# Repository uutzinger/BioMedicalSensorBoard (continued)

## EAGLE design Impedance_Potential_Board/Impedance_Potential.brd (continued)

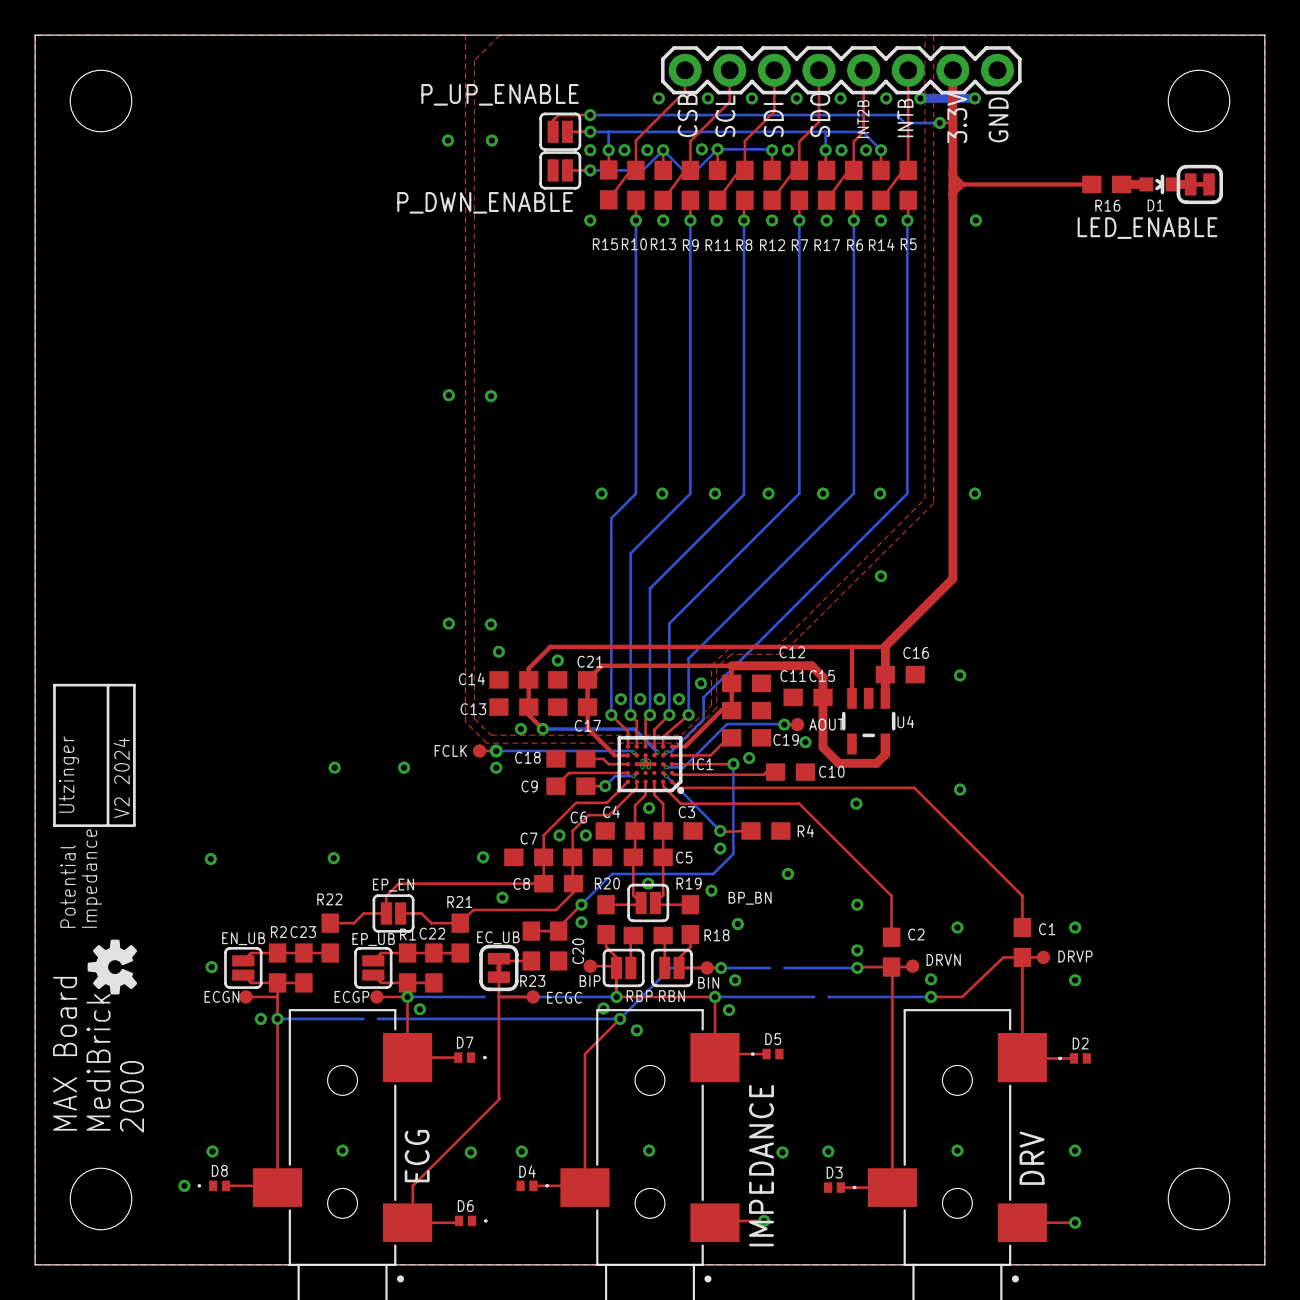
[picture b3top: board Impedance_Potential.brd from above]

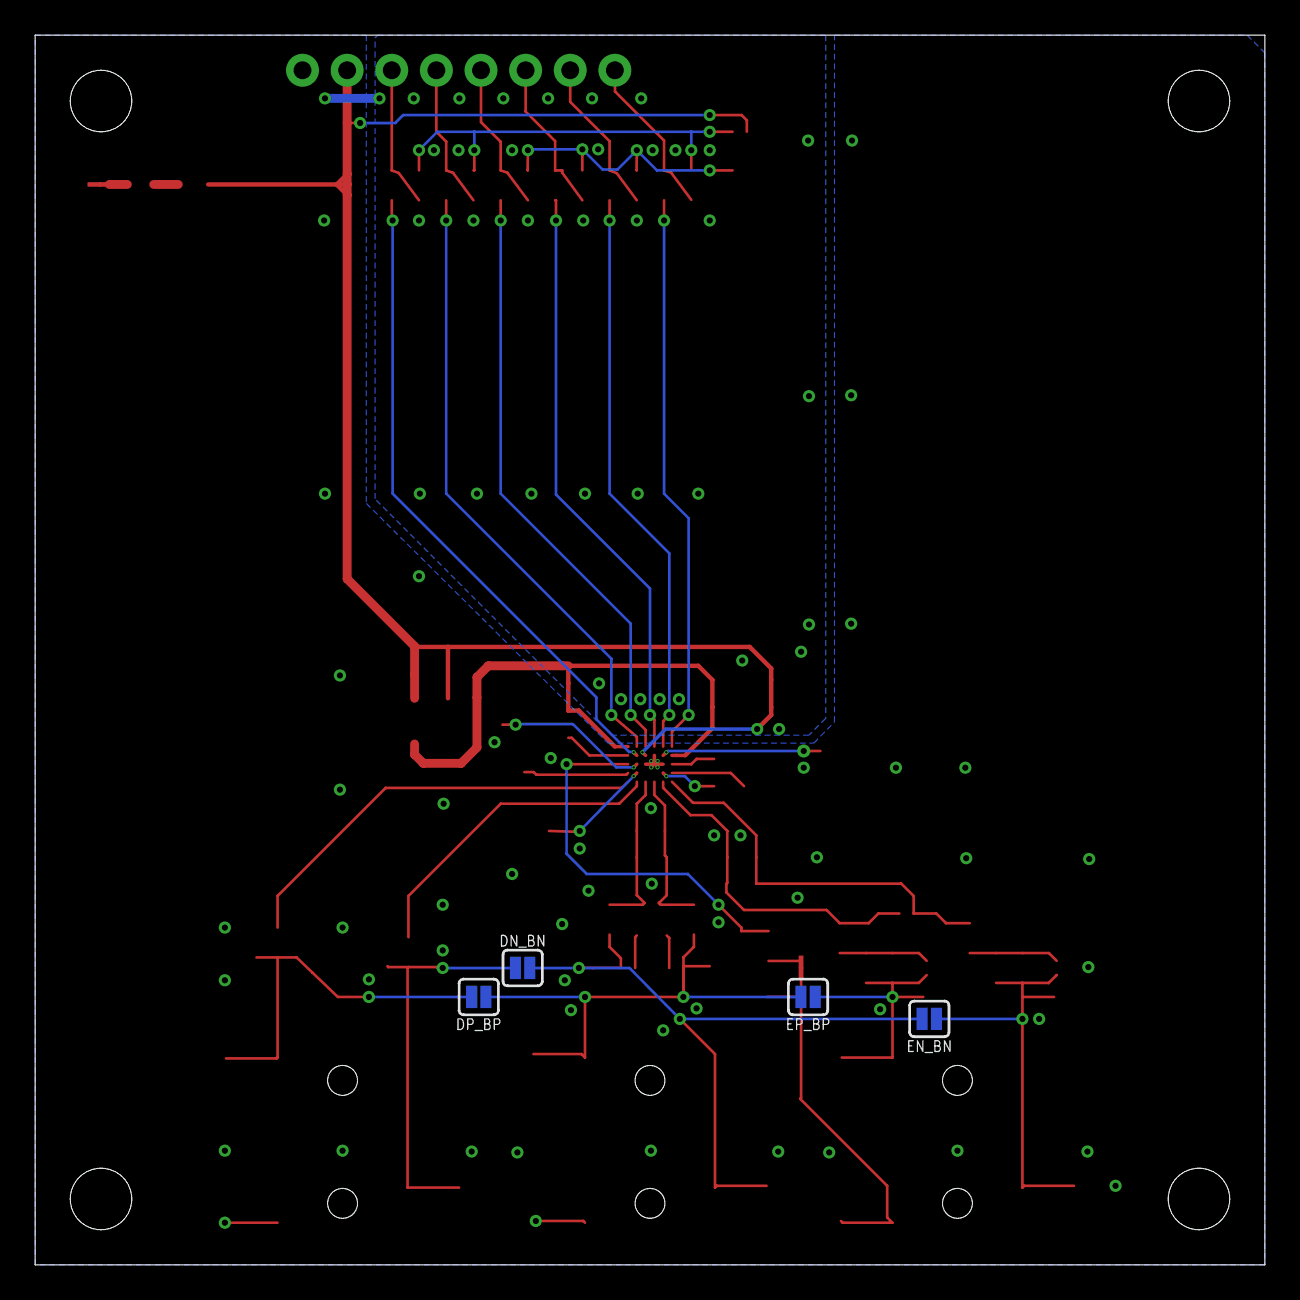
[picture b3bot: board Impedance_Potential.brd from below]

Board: 2 copper layers, 70.0 x 70.0 mm, 84 parts (4 on the bottom side), 46 nets.

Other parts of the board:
U$1: OSHW-LOGO-S

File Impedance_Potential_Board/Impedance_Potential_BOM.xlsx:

Item # | Designator | Qty | Manufacturer | Mfg Part # | LCSC Part# | U.S. Distributor | Description / Value | Packaging | Type | Cost
1 | C1, C2 | 2 | Samsung Electro-Mechanics | CL10B224KA8NNNC | C21120 |  | 0.22uF Ceramic Capacitor >=25V | 603 | SMD | 0.0052
2 | C3, C4, C6, C7 | 4 | Samsung Electro-Mechanics | CL10C100JB8NNNC | C1634 |  | 10pF Ceramic Capacitor >=25V | 603 | SMD | 0.0053
3 | C5 | 1 | Samsung Electro-Mechanics | CL10C470JB8NNNC | C1671 |  | 47pF Ceramic Capacitor >=25V | 603 | SMD | 0.006
4 | C8 | 1 | Samsung Electro-Mechanics | CL10B222KB8NNNC | C16033 |  | 2.2nF Ceramic Capacitor >=25V | 603 | SMD | 0.0057
5 | C9, C12, C14, C19, C20, C21 | 6 | Samsung Electro-Mechanics | CL10A106MA8NRNC | C96446 |  | 10uF Ceramic Capacitor >=25V | 603 | SMD | 0.0169
6 | C10, C15, C16 | 3 | Samsung Electro-Mechanics | CL10A105KB8NNNC | C15849 |  | 1.0uF Ceramic | 603 | SMD | 0.0042
7 | C11, C13, C17 | 3 | Samsung Electro-Mechanics | CL10B104KB8NNNC | C1591 |  | 0.1uF Ceramic Capacitor >=25V | 603 | SMD | 0.0024
8 | C18 | 1 | Samsung Electro-Mechanics | CL10B102KB8NNNC | C1588 |  | 1nF Ceramic Capacitor >= 25V | 603 | SMD | 0.0027
9 | C22, C23 | 2 | Samsung Electro-Mechanics | CL10B473KB8NNNC | C1622 |  | 47nF Ceramic Capacitor >=25V | 603 | SMD | 0.0043
10 | R1, R2 | 2 | YAGEO | RC0603FR-0751KL | C107231 |  | 51k 100mW Resistor | 603 | SMD | 0.0012
11 | R4 | 1 | YAGEO | RT0603BRE07324KL | C861836 |  | 324k 100mW Resistor | 603 | SMD | 0.019
12 | R5, R6, R7, R8, R9, R10 | 6 | YAGEO | RC0603JR-0710RL | C109317 |  | 10 100mW Resistor | 603 | SMD | 0.0019
13 | R11, R12, R13, R14, R15, R17 | 6 | YAGEO | RC0603FR-07100KL | C14675 |  | 100k 100mW Resistor | 603 | SMD | 0.0009
14 | R16 | 1 | YAGEO | RC0603FR-071KL | C22548 |  | 1k 100mW Resistor | 603 | SMD | 0.0009
15 | R18 | 1 | YAGEO | RC0603JR-07100RL | C110091 |  | 100 100mW Resistor | 603 | SMD | 0.0011
16 | R19, R20, R21, R22 | 4 | YAGEO | RC0603JR-070RL | C95177 |  | 0 100mW Resistor | 603 | SMD | 0.001
17 | R23 | 1 | YAGEO | RT0603BRD07200KL | C728585 |  | 200k Resistor | 603 | SMD | 0.023
18 | D2, D3, D4, D5, D6, D7, D8 | 7 | onsemi | ESD7551N2T5G | C5123457 | https://www.mouser.com/ProductDetail/onsemi/ESD7551N2T5G?qs=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 | ESD7551N2T5G, Protection Diode | ESD7551N2T5G | SMD | 0.0932
19 | D1 | 1 | XINGLIGHT | XL-1608UBC-04 | C965807 |  | Blue LED | 603 | SMD | 0.0034
20 | IC1 | 1 | Analog Devices/Maxim | MAX30001GCWV+ |  | https://www.mouser.com/ProductDetail/Analog-Devices-Maxim-In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 | MAX30001GCWV+ | BGA30C50P6X5_293X274X69 | SMD | 10.44
21 | U4 | 1 | Diodes Incorporated | AP2112K-1.8TRG1 | C176944 | https://www.mouser.com/ProductDetail/Diodes-Incorporated/AP2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 | AP2112K-1.8V V_REG_LDO SMD | SOT-25 | SMD
22 | DRV, ECG, IMPEDANCE | 3 | CUI Devices | SJ-3523-SMT-TR | C4991872 | https://www.mouser.com/ProductDetail/CUI-Devices/SJ-3523-SMT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 | 3.5mm Audio Jack, Low Profils, Stereo 3 pin Right Angle | CUI_SJ-3523-SMT-TR | SMD | 1.01

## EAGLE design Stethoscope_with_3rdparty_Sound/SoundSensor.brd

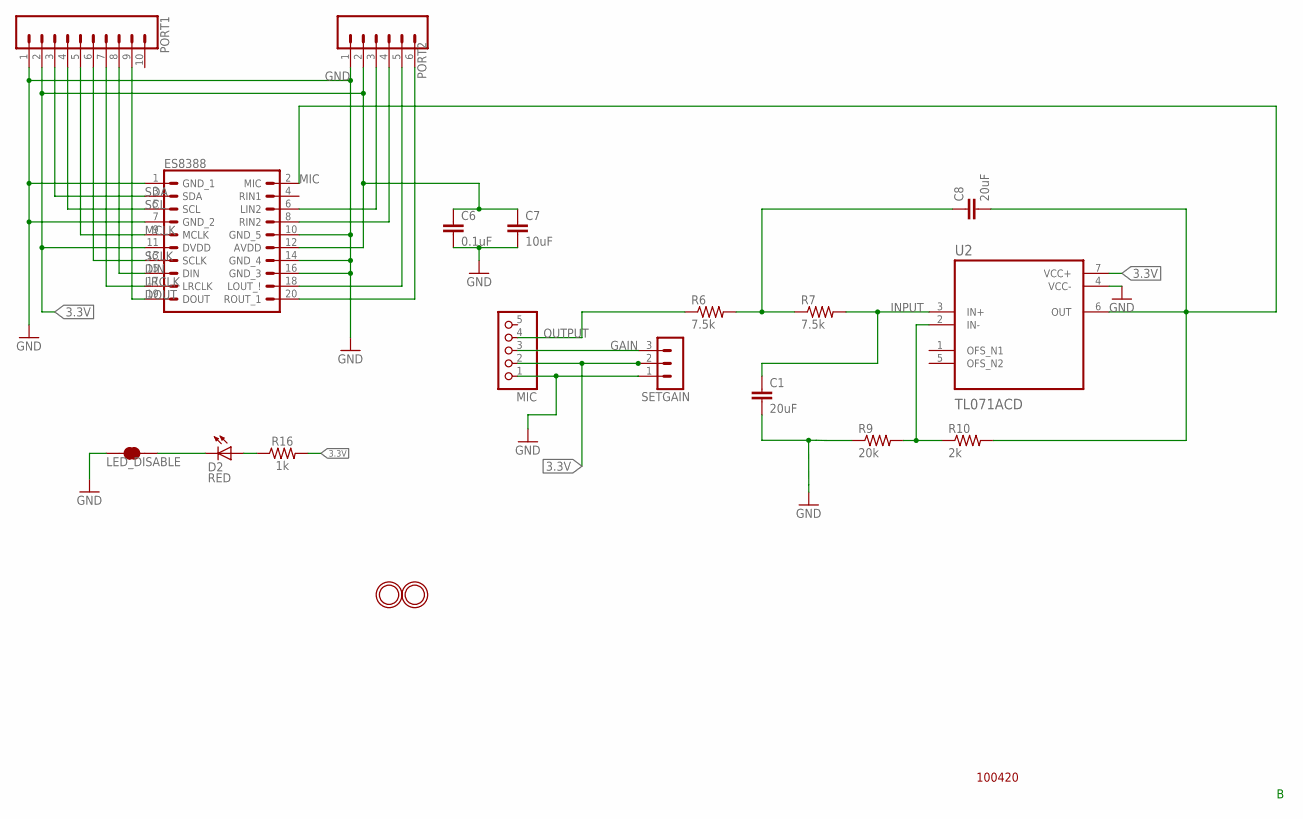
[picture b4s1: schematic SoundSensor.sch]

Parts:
C1, C8: 20uF; C0603
C6: 0.1uF; C0603
C7: 10uF; C0603
D2: RED; LED-0603
ES8388: ES8388ES8388; ES8388
LED_DISABLE: JUMPER-SMT_2_NC_TRACE_SILK; SMT-JUMPER_2_NC_TRACE_SILK
MIC: HEADER-1X576MIL; 1X05_ROUND_76
PORT1: CONN_10"; 1X10
PORT2: CONN_06SILK_FEMALE_PTH; 1X06
R6, R7: 7.5k; R0603
R9: 20k; R0603
R10: 2k; R0603
R16: 1k; 0603
SETGAIN: MA03-1
U2: TL071ACD; SOIC127P599X175-8N
U$1, U$5: MOUNTINGHOLE2.0; MOUNTINGHOLE_2.0_PLATED

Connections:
3.3V: C6.1, C7.1, ES8388.11 (DVDD), ES8388.12 (AVDD), MIC.2, PORT1.2, PORT2.2, R16.2, SETGAIN.2, U2.7 (VCC+)
DIN: ES8388.15 (DIN), PORT1.8
DOUT: ES8388.19 (DOUT), PORT1.9
GAIN: MIC.3, SETGAIN.3
GND: C1.2, C6.2, C7.2, ES8388.1 (GND_1), ES8388.7 (GND_2), ES8388.10 (GND_5), ES8388.14 (GND_4), ES8388.16 (GND_3), LED_DISABLE.1, MIC.1, PORT1.1, PORT2.1, R9.1, SETGAIN.1, U2.4 (VCC-)
INPUT: C1.1, R7.2, U2.3 (IN+)
LRCLK: ES8388.17 (LRCLK), PORT1.7
MCLK: ES8388.9 (MCLK), PORT1.5
MIC: C8.2, ES8388.2 (MIC), R10.2, U2.6 (OUT)
unnamed: ES8388.6 (LIN2), PORT2.3
unnamed: ES8388.8 (RIN2), PORT2.4
unnamed: ES8388.18 (LOUT_!), PORT2.5
unnamed: ES8388.20 (ROUT_1), PORT2.6
unnamed: C8.1, R6.2, R7.1
unnamed: R9.2, R10.1, U2.2 (IN-)
unnamed: D2.A, R16.1
unnamed: D2.C, LED_DISABLE.2
OUTPUT: MIC.4, R6.1
SCL: ES8388.5 (SCL), PORT1.4
SCLK: ES8388.13 (SCLK), PORT1.6
SDA: ES8388.3 (SDA), PORT1.3

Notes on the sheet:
100420

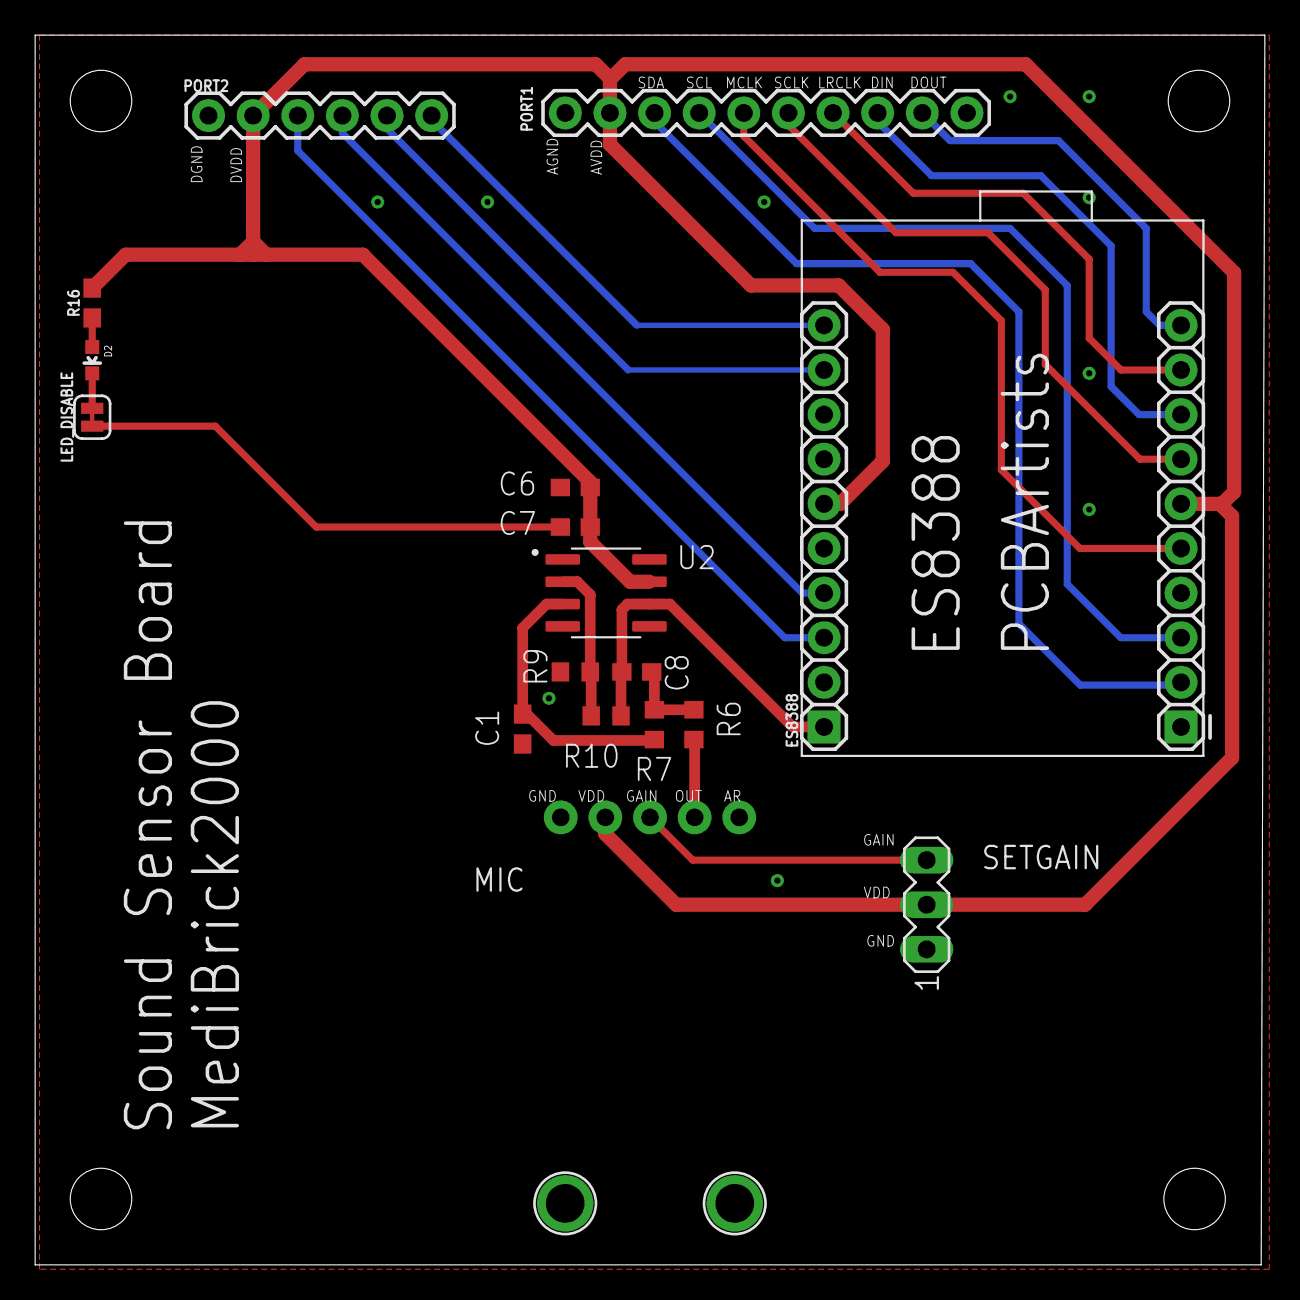
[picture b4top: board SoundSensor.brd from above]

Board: 2 copper layers, 70.0 x 70.0 mm, 19 parts (0 on the bottom side), 21 nets.

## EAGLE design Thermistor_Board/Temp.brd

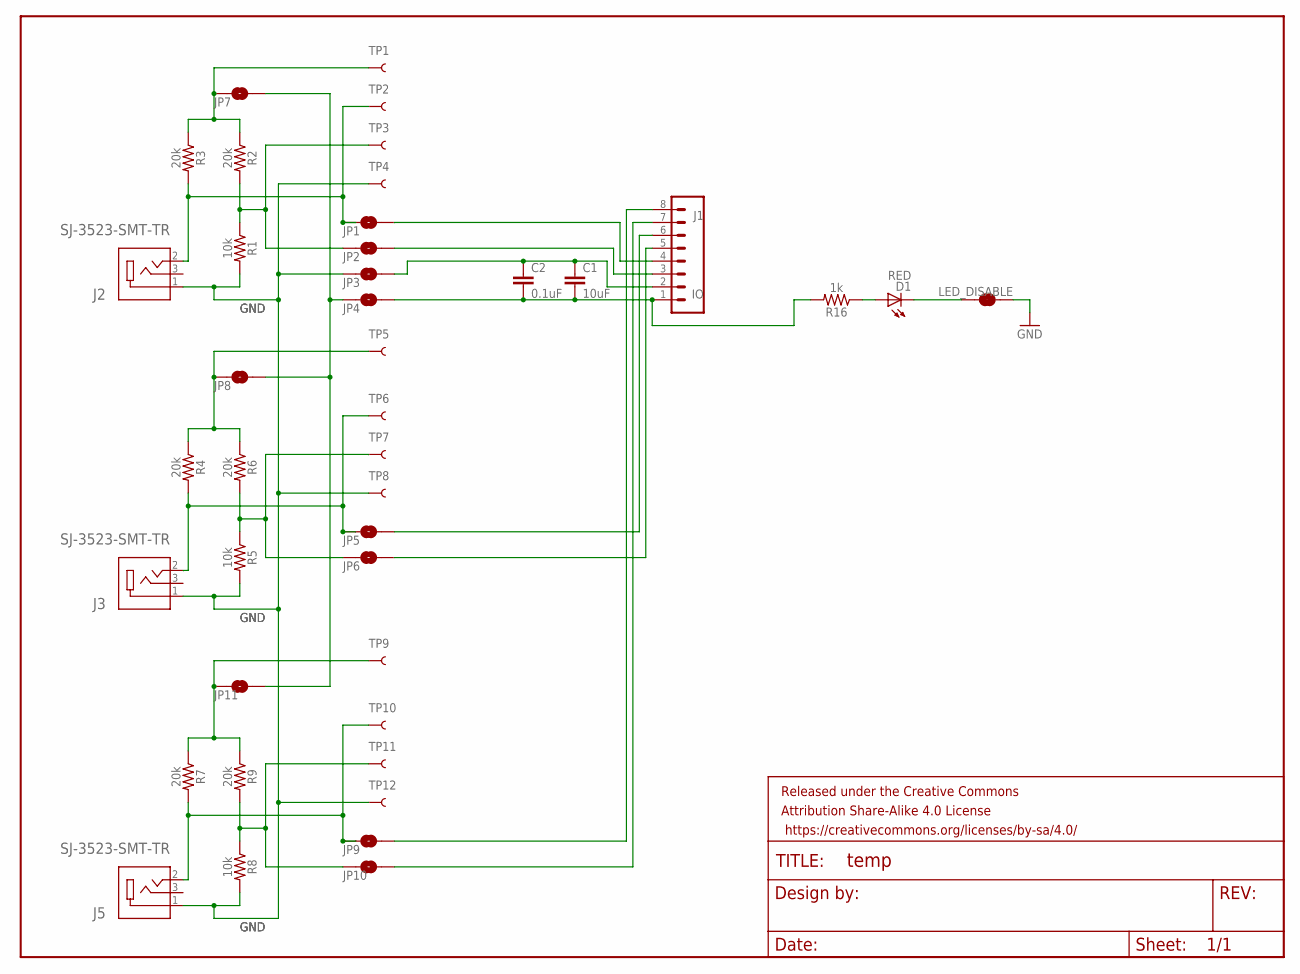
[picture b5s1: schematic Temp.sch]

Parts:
C1: 10uF; 0603
C2: 0.1uF; 0603
D1: RED; LED-0603
FRAME1: FRAME-LETTERNO_PACKAGE; DUMMY
J1: IO; 1X08
J2, J3, J5: SJ-3523-SMT-TR; CUI_SJ-3523-SMT-TR
JP1, JP2, JP3, JP4, JP5, JP6, JP7, JP8, JP9, JP10, JP11: JUMPER-SMT_2_NO_NO-SILK; SMT-JUMPER_2_NO_NO-SILK
LED_DISABLE: JUMPER-SMT_2_NC_TRACE_SILK; SMT-JUMPER_2_NC_TRACE_SILK
R1, R5, R8: 10k; 0603
R2, R3, R4, R6, R7, R9: 20k; 0603
R16: 1k; 0603
TP1, TP2, TP3, TP4, TP5, TP6, TP7, TP8, TP9, TP10, TP11, TP12: TEST-POINT3X5; PAD.03X.05

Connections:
3.3V: JP4.1, JP7.2, JP8.2, JP11.2
GND: J2.1, J3.1, J5.1, JP3.1, LED_DISABLE.1, R1.2, R5.2, R8.2, TP4.P$1, TP8.P$1, TP12.P$1
unnamed: JP6.1, R5.1, R6.2, TP7.P$1
unnamed: J1.5, JP6.2
unnamed: JP2.1, R1.1, R2.2, TP3.P$1
unnamed: JP7.1, R2.1, R3.1, TP1.P$1
unnamed: J1.3, JP2.2
unnamed: J2.2, JP1.1, R3.2, TP2.P$1
unnamed: J1.4, JP1.2
unnamed: J3.2, JP5.1, R4.2, TP6.P$1
unnamed: J1.7, JP10.2
unnamed: J1.8, JP9.2
unnamed: J1.6, JP5.2
unnamed: JP8.1, R4.1, R6.1, TP5.P$1
unnamed: JP10.1, R8.1, R9.2, TP11.P$1
unnamed: J5.2, JP9.1, R7.2, TP10.P$1
unnamed: C1.1, C2.1, J1.2, JP3.2
unnamed: JP11.1, R7.1, R9.1, TP9.P$1
unnamed: C1.2, C2.2, J1.1, JP4.2, R16.2
unnamed: D1.A, R16.1
unnamed: D1.C, LED_DISABLE.2

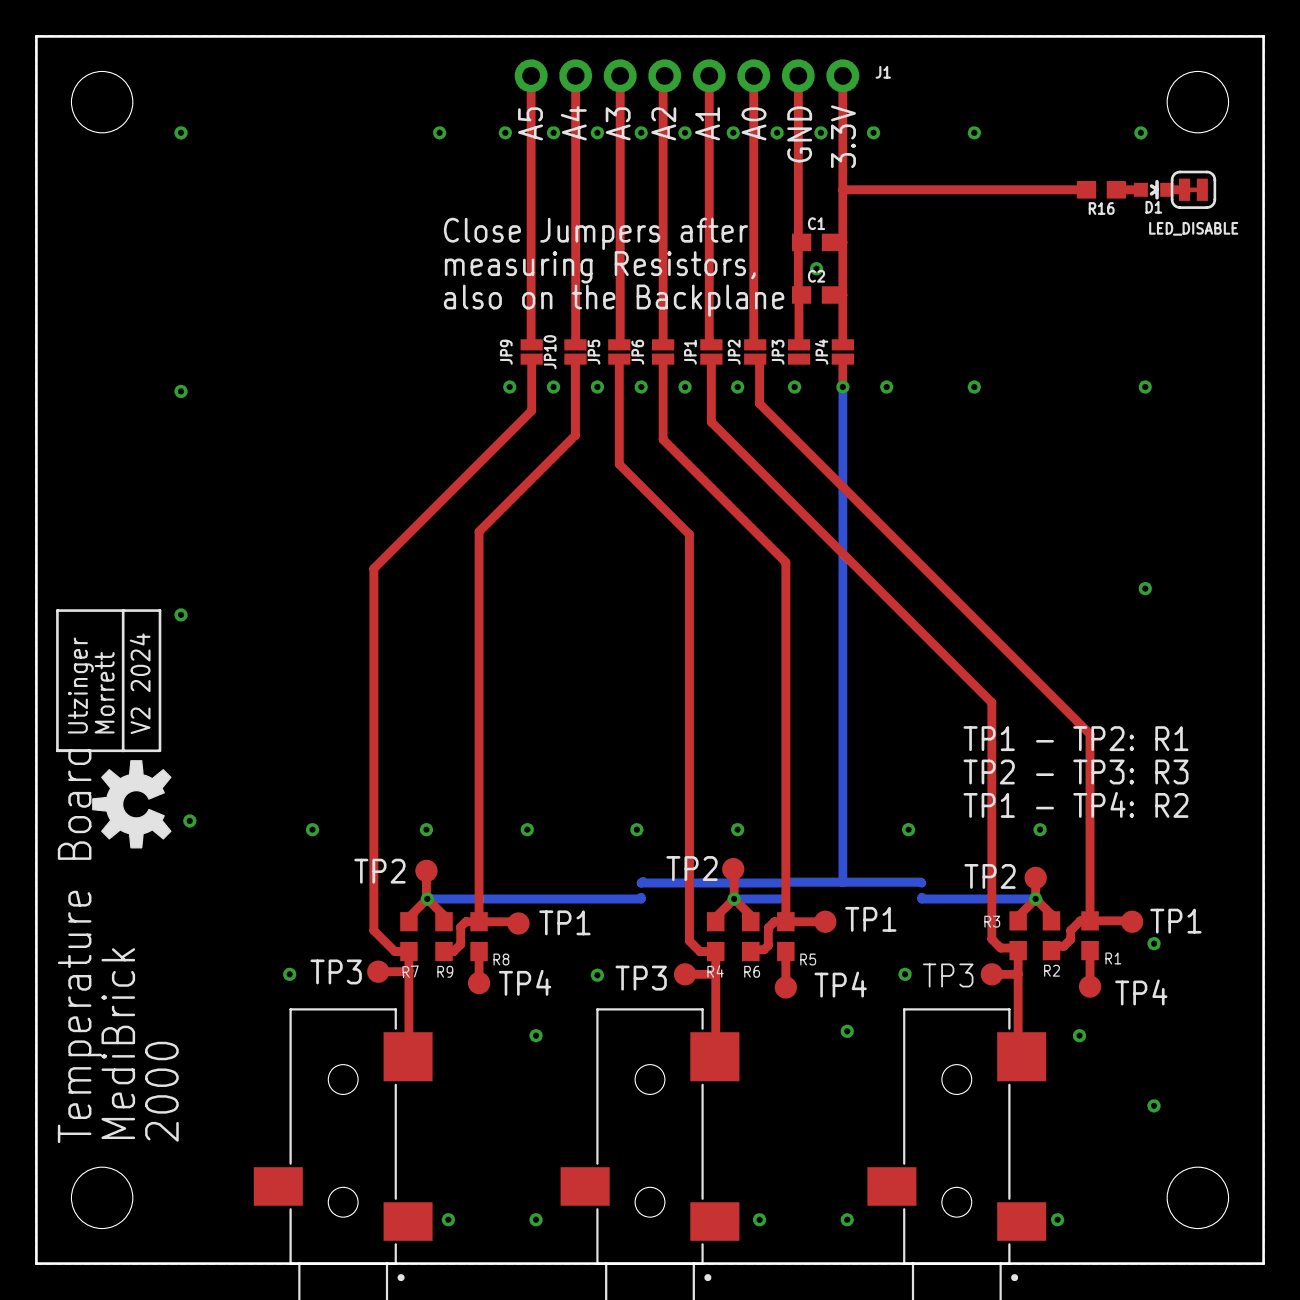
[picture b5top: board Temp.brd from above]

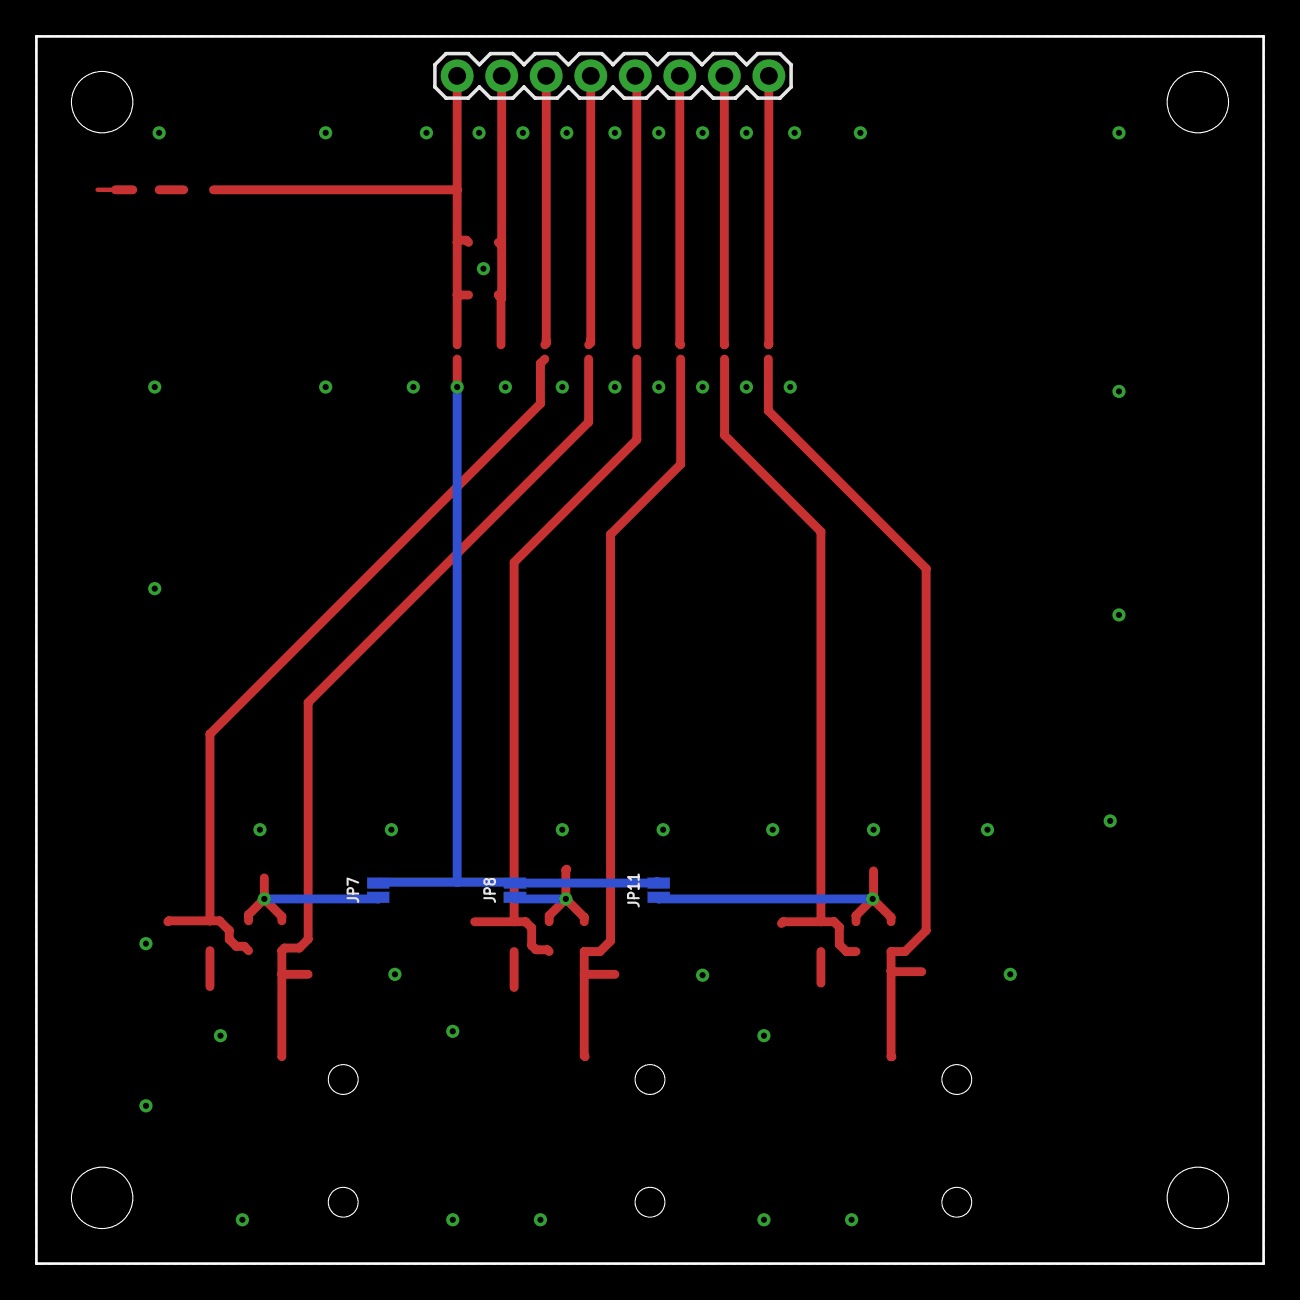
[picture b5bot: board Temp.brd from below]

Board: 2 copper layers, 70.0 x 70.0 mm, 43 parts (4 on the bottom side), 21 nets.

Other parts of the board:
U$1: OSHW-LOGO-M

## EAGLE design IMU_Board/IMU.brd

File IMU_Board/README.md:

# IMU MediBrick

This board is based on latest TDK IMU [ICM20948](datasheest/DS-000189-ICM-20948-v1.3.pdf) and BOSCH precision pressure sensors [BMP581](datasheets/BSS138-D.pdf) and uses SPI interface accommodating a sampling rate exceeding 1000 samples per second.

## Costs &#36;

| Item        | Quantity at Purchase | Costs  | Source            | Cost per Brick
|---                          | ---  | ---    | ---               | ---
| Microcontroller             |  1   | $17.5  | [Adafruit](https://www.adafruit.com/product/5477)          | $17.5
| Display                     |  5   | $13    | [Amazon](https://a.co/d/1QH0Ab9)            | $3
| Button                      | 25   | $9     | [Amazon](https://a.co/d/8KAuTwC) | $0.5 
| Battery                     |  1   | $10     | [Adafruit](https://www.adafruit.com/product/258)        | $10
| PCB                         |  5   | $45.20  | PCBWay            | $9
| Parts and Assembly          |  2   | $51.87* | PCBWay            | $26
| Assorted Wires              |8m    | $15    | [Amazon](https://a.co/d/58djefc) | $1
| Assorted Screws and Nuts    |100   |  $7    | Amazon            | $0.05
| Assorted 3D printed parts   |      |        |  | $3
|                             |      |        |                   |
| **Total**                   |      |        |                   | **$70**

*Electronic components are $11 per board. 

## Test Software &#128187;
Test software is located in the Arduino folder.

| Folder | Description | 
|--- |---|
|MediBrick_IMU_ICM20948_DMP_Test | IMU with onboard attitude calculation. |
|MediBrick_IMU_P_BMP581_Interrupt| Pressure sensor with interrupt. |

## Microcontroller Software : &#9000;
Not finalized yet

## Electronics Design &#128268;

The following files are needed for PCB manufacturing and assembly.

- [Bill of Materials](IMU_BOM.xlsx)
- [Manufacturing Files](IMU_2024-08-03.zip)
- [Pick and Place](IMU_PnP.xlsx)

The Bill of Materials is formatted so that its compatible with PCBWay submissions.

## 3D Printed Parts &#9881;
These are the links to the OnShape Design files, which you can edit and modify if you have an OnShape account (OnShape has free academic accounts).

- Medi Brick
  - [Brick Top](https://cad.onshape.com/documents/be6b7e5f847d89f3ec5eb9d5/w/761fee9865ca7ef709028476/e/ff897b4f359cec83b782ff14)
  - [Brick Bottom](https://cad.onshape.com/documents/92ad78475e8f0b17ff5e260b/w/88a02abbcb12cdbd4d9de3ad/e/fb79ca58ad2b6a0298e9d1b6)
  - [Brick Assembly](https://cad.onshape.com/documents/11cbfe9c3c739b6e8ecbf3d7/w/989b564ecd7f6d069e643ac0/e/85542f706be8cc7554218e8d)
  - [IMU Brick Side Plate](https://cad.onshape.com/documents/eb58e78174fdb2053487973b/w/903e17c4126fb90e8782ab92/e/f4b50a954b0de64bf397a15c?renderMode=0&uiState=6712e42015dc976491f468b3)

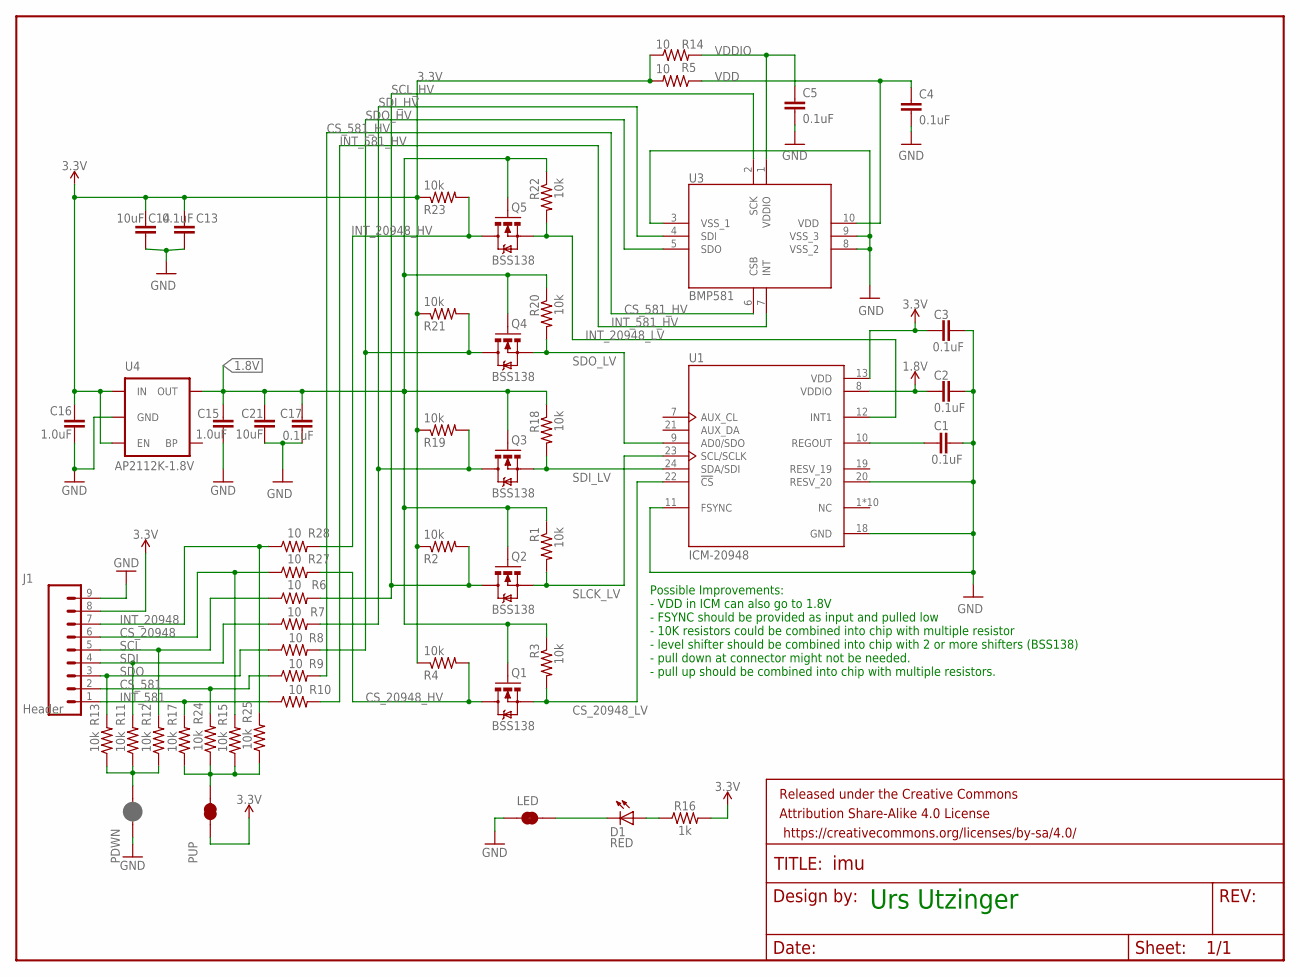
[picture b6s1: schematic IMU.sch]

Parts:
C1, C2, C3, C4, C5, C13, C17: 0.1uF; 0603
C14, C21: 10uF; 0603@1
C15, C16: 1.0uF; 0603
D1: RED; LED-0603
FRAME1: FRAME-LETTERNO_PACKAGE; DUMMY
J1: Header; 1X09
LED: LED ENABLE; SMT-JUMPER_2_NC_TRACE_SILK
PDWN: JUMPER-SMT_2_NC_PASTE_SILK; SMT-JUMPER_2_NC_PASTE_SILK
PUP: JUMPER-SMT_2_NC_TRACE_SILK; SMT-JUMPER_2_NC_TRACE_SILK
Q1, Q2, Q3, Q4, Q5: BSS138; SPARKFUN_SOT23-3
R1, R2, R3, R4, R11, R12, R13, R15, R17, R18, R19, R20, R21, R22, R23, R24, R25: 10k; 0603
R5, R6, R7, R8, R9, R10, R14, R27, R28: 10; 0603
R16: 1k; 0603
U1: ICM-20948; QFN40P300X300X105-24N
U3: BMP581
U4: AP2112K-1.8V; SPARKFUN-POWERIC_SOT23-5

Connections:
1.8V: C2.1, C15.2, C17.1, C21.1, Q1.1 (G), Q2.1 (G), Q3.1 (G), Q4.1 (G), Q5.1 (G), R1.1, R3.1, R18.1, R20.1, R22.1, U1.8 (VDDIO), U4.5 (OUT)
3.3V: C3.1, C13.1, C14.1, C16.2, J1.8, PUP.1, R2.1, R4.1, R5.2, R14.1, R16.2, R19.1, R21.1, R23.1, U1.13 (VDD), U4.1 (IN), U4.3 (EN)
CS_581: J1.2, R9.1, R24.2
CS_581_HV: R9.2, U3.6 (CSB)
CS_20948: J1.6, R15.2, R27.1
CS_20948_HV: Q1.3 (D), R4.2, R27.2
CS_20948_LV: Q1.2 (S), R3.2, U1.22 (!CS)
GND: C1.2, C2.2, C3.2, C4.2, C5.2, C13.2, C14.2, C15.1, C16.1, C17.2, C21.2, J1.9, LED.1, PDWN.1, U1.11 (FSYNC), U1.18 (GND), U1.20 (RESV_20), U3.3 (VSS_1), U3.8 (VSS_2), U3.9 (VSS_3), U4.2 (GND)
INT_581: J1.1, R10.1, R17.2
INT_581_HV: R10.2, U3.7 (INT)
INT_20948: J1.7, R25.2, R28.1
INT_20948_HV: Q5.3 (D), R23.2, R28.2
INT_20948_LV: Q5.2 (S), R22.2, U1.12 (INT1)
unnamed: C1.1, U1.10 (REGOUT)
unnamed: D1.A, R16.1
unnamed: D1.C, LED.2
unnamed: PDWN.2, R11.1, R12.1, R13.1
unnamed: PUP.2, R15.1, R17.1, R24.1, R25.1
SCL: J1.5, R6.1, R12.2
SCL_HV: Q2.3 (D), R2.2, R6.2, U3.2 (SCK)
SDI: J1.4, R7.1, R11.2
SDI_HV: Q3.3 (D), R7.2, R19.2, U3.4 (SDI)
SDI_LV: Q3.2 (S), R18.2, U1.24 (SDA/SDI)
SDO: J1.3, R8.1, R13.2
SDO_HV: Q4.3 (D), R8.2, R21.2, U3.5 (SDO)
SDO_LV: Q4.2 (S), R20.2, U1.9 (AD0/SDO)
SLCK_LV: Q2.2 (S), R1.2, U1.23 (SCL/SCLK)
VDD: C4.1, R5.1, U3.10 (VDD)
VDDIO: C5.1, R14.2, U3.1 (VDDIO)

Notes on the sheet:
Urs Utzinger
Possible Improvements: - VDD in ICM can also go to 1.8V - FSYNC should be provided as input and pulled low - 10K resistors could be combined into chip with multiple resistor - level shifter should be combined into chip with 2 or more shifters (BSS138) - pull down at connector might not be needed. -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

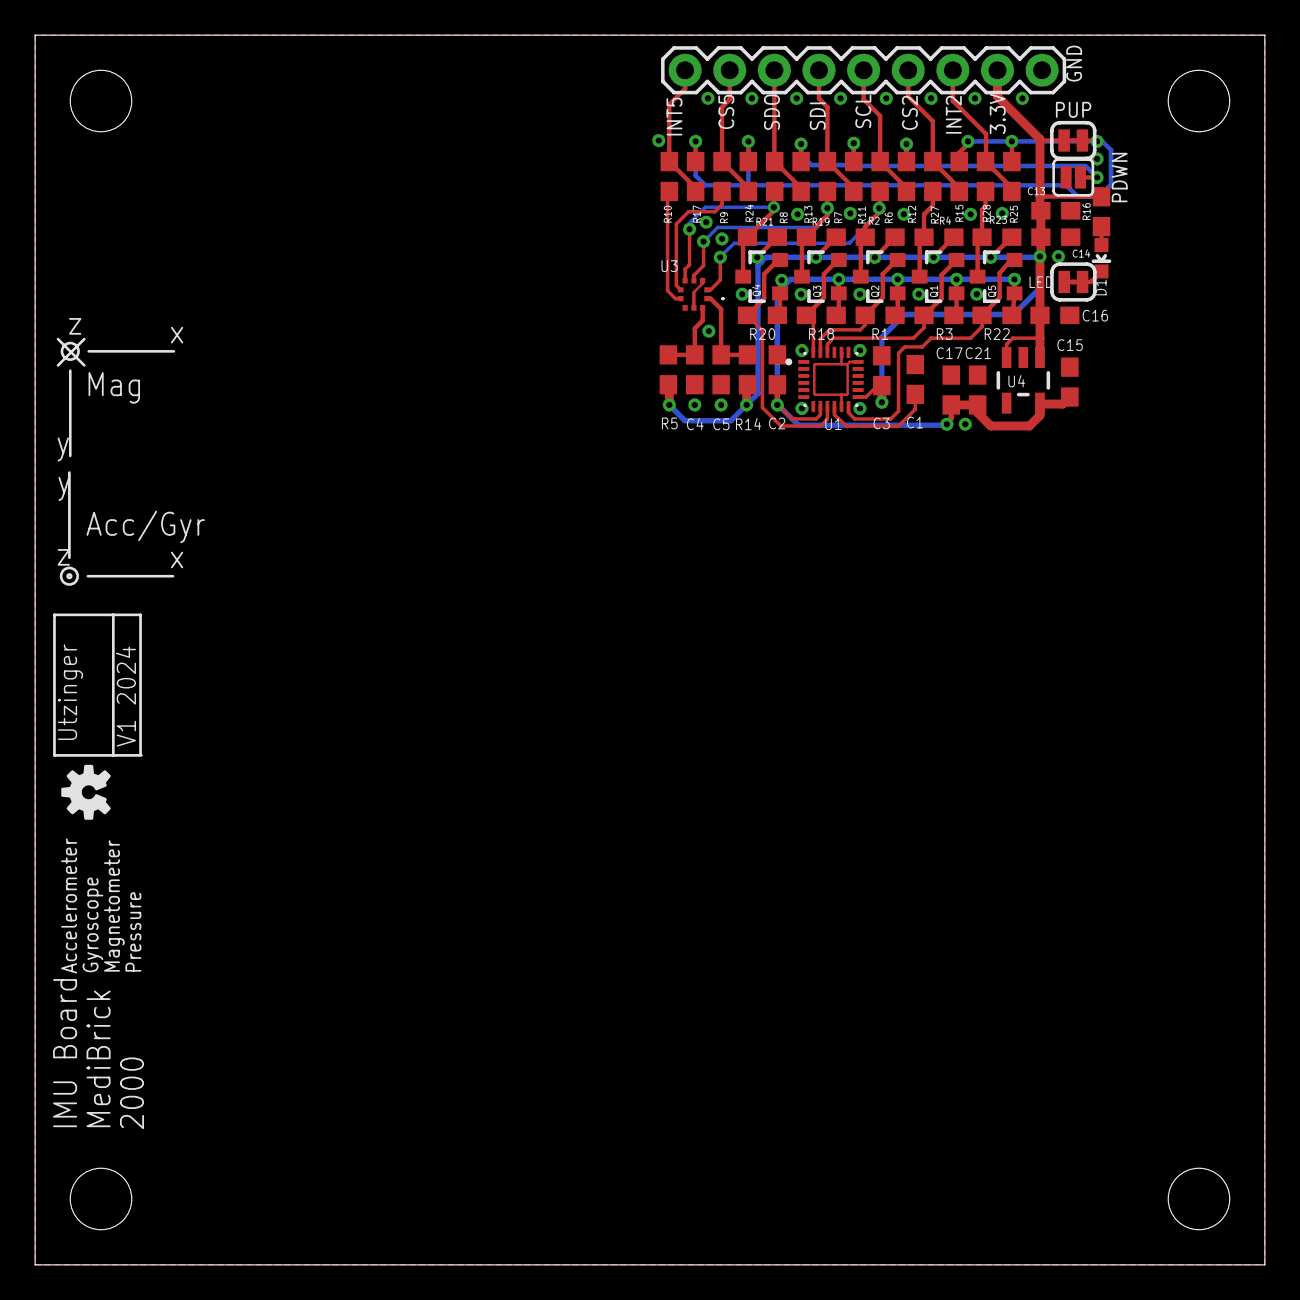
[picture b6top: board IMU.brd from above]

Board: 2 copper layers, 70.0 x 70.0 mm, 53 parts (0 on the bottom side), 29 nets.

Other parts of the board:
U$1: OSHW-LOGO-S

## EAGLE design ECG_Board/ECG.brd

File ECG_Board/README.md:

This is a description for ECG Sensor from the capstone project: https://github.com/grender007/Modular-Biomedical-Sensor-Board-for-Education

The ECG Module takes advantage of the Sparkfun ECG Pre-Amplifier Board. It uses the AD8232 IC to detect the voltage potential of the heart. 
The microcontroller's analog to digital converter is needed to record the signal.

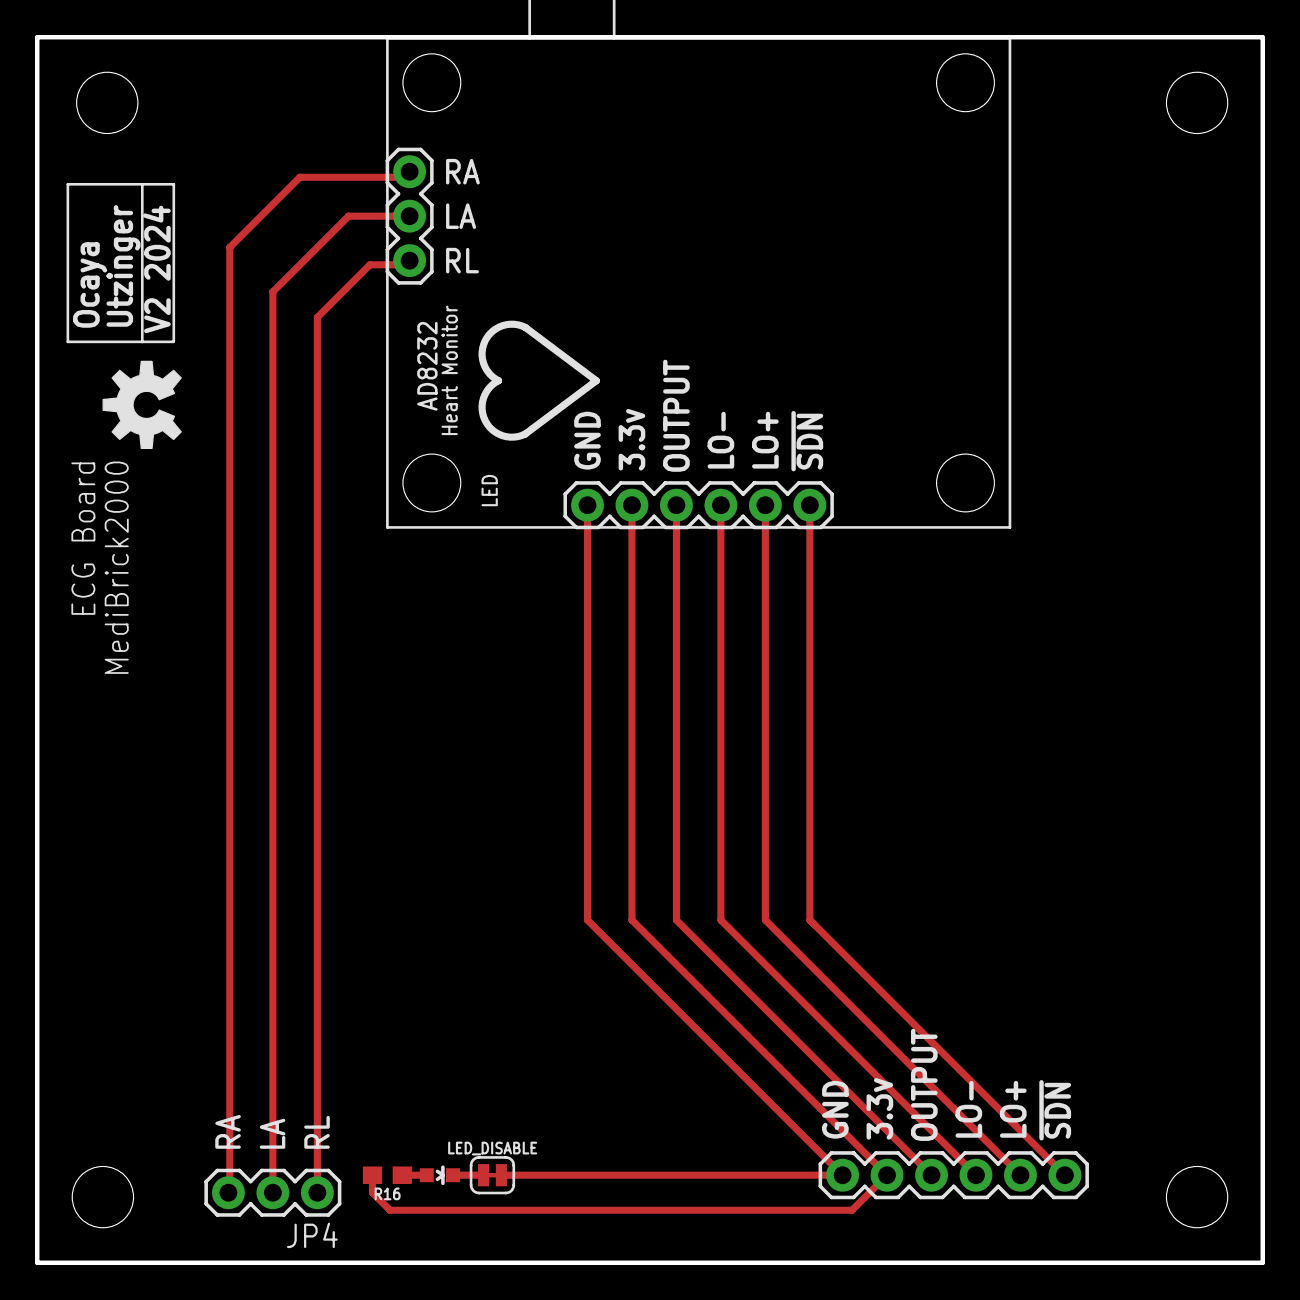
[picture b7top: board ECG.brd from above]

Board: 2 copper layers, 70.0 x 70.0 mm, 8 parts (0 on the bottom side), 11 nets.

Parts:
D1: RED; LED-0603
FRAME1: FRAME-LETTERNO_PACKAGE; DUMMY
JP2: 1X06
JP4: 1X03
LED_DISABLE: JUMPER-SMT_2_NC_TRACE_SILK; SMT-JUMPER_2_NC_TRACE_SILK
R16: 1k; 0603
U$1: SPARK_ECG
U$2: OSHW-LOGO-M

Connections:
3.3V: JP2.2, R16.2, U$1.2
GND: JP2.1, LED_DISABLE.1, U$1.1
unnamed: JP4.1, U$1.7
unnamed: JP4.2, U$1.8
unnamed: JP4.3, U$1.9
unnamed: JP2.6, U$1.6
unnamed: JP2.5, U$1.5
unnamed: JP2.4, U$1.4
unnamed: JP2.3, U$1.3
unnamed: D1.A, R16.1
unnamed: D1.C, LED_DISABLE.2
